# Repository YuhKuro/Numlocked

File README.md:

# Numlocked: Shift
 A 75% + 25% Keyboard with extras
 ## Features:
 - "standard" 75% ANSI US QWERTY Layout
 - Hot Swappable
 - Integrated Fingerprint Sensor
 - Leftside Numpad
 - Volume Knob, Dedicated Media Keys
 - Four extra keys above the keypad, nine extra F keys. 
 - Separate USB hub with two USB-A ports and one USB-C connection
 - 128x32 OLED
 
Front of Keyboard PCB:

Back of keyboard PCB:

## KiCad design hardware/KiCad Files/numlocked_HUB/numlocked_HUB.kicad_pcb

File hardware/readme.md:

# Hardware

## Table of Contents
- [Introduction](#introduction)
- [Keyboard Fundamentals](#keyboard-fundamentals)
- [HUB PCB](#hub-pcb)
- [Leftside PCB](#left-side-pcb)
- [Rightside PCB](#right-side-pcb)
- [Numpad PCB](numpad-pcb)

## Introduction
The keyboard consists of four PCBs: A USB-Hub and three PCBs for each part of the keyboard: Leftside, Rightside and Numpad.
Each component is connected via magnetic pogo pins to transmit Power, Ground, keyboard signals and LED signals.

## Keyboard Fundamentals
Although most keyboards use a matrix-and-diode system, this keyboard uses a Parallel-load Serial-Shift shift-register approach.

Think of it like a train with containers moving along a circular track. Each container represents a key position, and the train can either load or shift its contents.

When the train is in "Load" mode, each container is set based on whether its corresponding key is pressed. If a key is not pressed, the container remains full; if it's pressed, the container will empty its contents out. 

In "Shift" mode, the train moves each container along, allowing us to check them one by one and identify which keys are pressed by checking which containers are empty.

In this keyboard, all shift registers are pulled up to 3V3 through a 10k-ohm resistor, so each key naturally sits at a high (3.3V) state, much like a full train car. When a key is pressed, it ground that bit on the shift register, reading it as low. By shifting the bits in the register the exact number of keys and feeding the information into an array, we will have a snapshot of what keys are pressed in that cycle. 

Since the SN74HC165DR Shift Registers used in this keyboard allow clocking in the range of a few MHz, there is practically zero chance a key input is missed as the next "load" phase is a just a few microseconds away.

This system also allows for minimal debouncing, requires zero diodes, only requires three pins to read any number of keys and true n-key rollover.

### Why this method?
Using shift registers allows for overall less individual soldering, easier programming and most importantly, only requires three pins (SH/~LD, CLK and Serial-Out).
If we chain shift registers beginning with the removable parts, such as the numpad, and transmit the serial-out to the next removable part, such as the right side, and finally to the left-side, we can manage a system with only one MCU by using multiplexers to avoid unknown values. 

We can do this by using multiplexers, which are basically data switches, and schmitt triggers which help ensure a clear signal. By using the schmitt triggers, the multiplexers always have a clean input on which component is connected. 

The flow chart into the first shift register of the left side is the following:

The edge case of numpad connected, but no right side is handled in software.

## Hub PCB
The Hub PCB is centered around a one-to-four USB 2.0 Full Speed HUB. There is one upstream USB-C port which connects to the user's computer and three USB-A ports for other peripherals, as well as an FFC cable which connects it to the keyboard itself.

To minimize space used in the case, there is a notched hole on the PCB itself to allow the FFC Cable to connect between the Hub to the keyboard PCB even when the two PCBs may be flush.

## Left-Side PCB
The Left-Side PCB serves as the core of the keyboard’s functionality and is the only component capable of operating independently. This is due to the onboard RP2040 microcontroller, which manages all keyboard input processing. The Left-Side PCB features an FFC connector linking it to the USB Hub PCB, enabling seamless integration within the keyboard assembly.
The Left-Side PCB Features:
- FFC Connector to connect to the Hub
- RP2040 Microcontroller
	- 128 Mbit SPI Flash Memory
	- Crystal Oscillator
	- Header pins for Reset and USB Boot
- Five SN74HC165DR parallel-load serial-out shift registers to handle inputs
- Two four-pin magnetic pogo pins (2x4) to connect to the Numpad PCB.
- Three four-pin magnetic pogo pins (3x4) to connect to the Right-Side PCB
- Muxes and Debouncing Schmitt Triggers
- Real-time Clock (RTC) and CR1220 coin battery
### RP2040
The MCU for this keyboard is the RP2040, select for its cost, power efficiency and ease-of-programming, along with its plethora of GPIO pins and IO options. 

## Right-Side PCB
The Right-side PCB handles the right side of the keyboard's inputs and passes it the left-side of the keyboard.
Furthermore, the Right-Side PCB (if present) will also pass through the Numpad's data to the left side of the keyboard. This design was chosen to minimize the number of Magnetic Pogo Pin Connectors
## Numpad PCB
The Numpad PCB contains much of the same components as the Left-Side PCB.

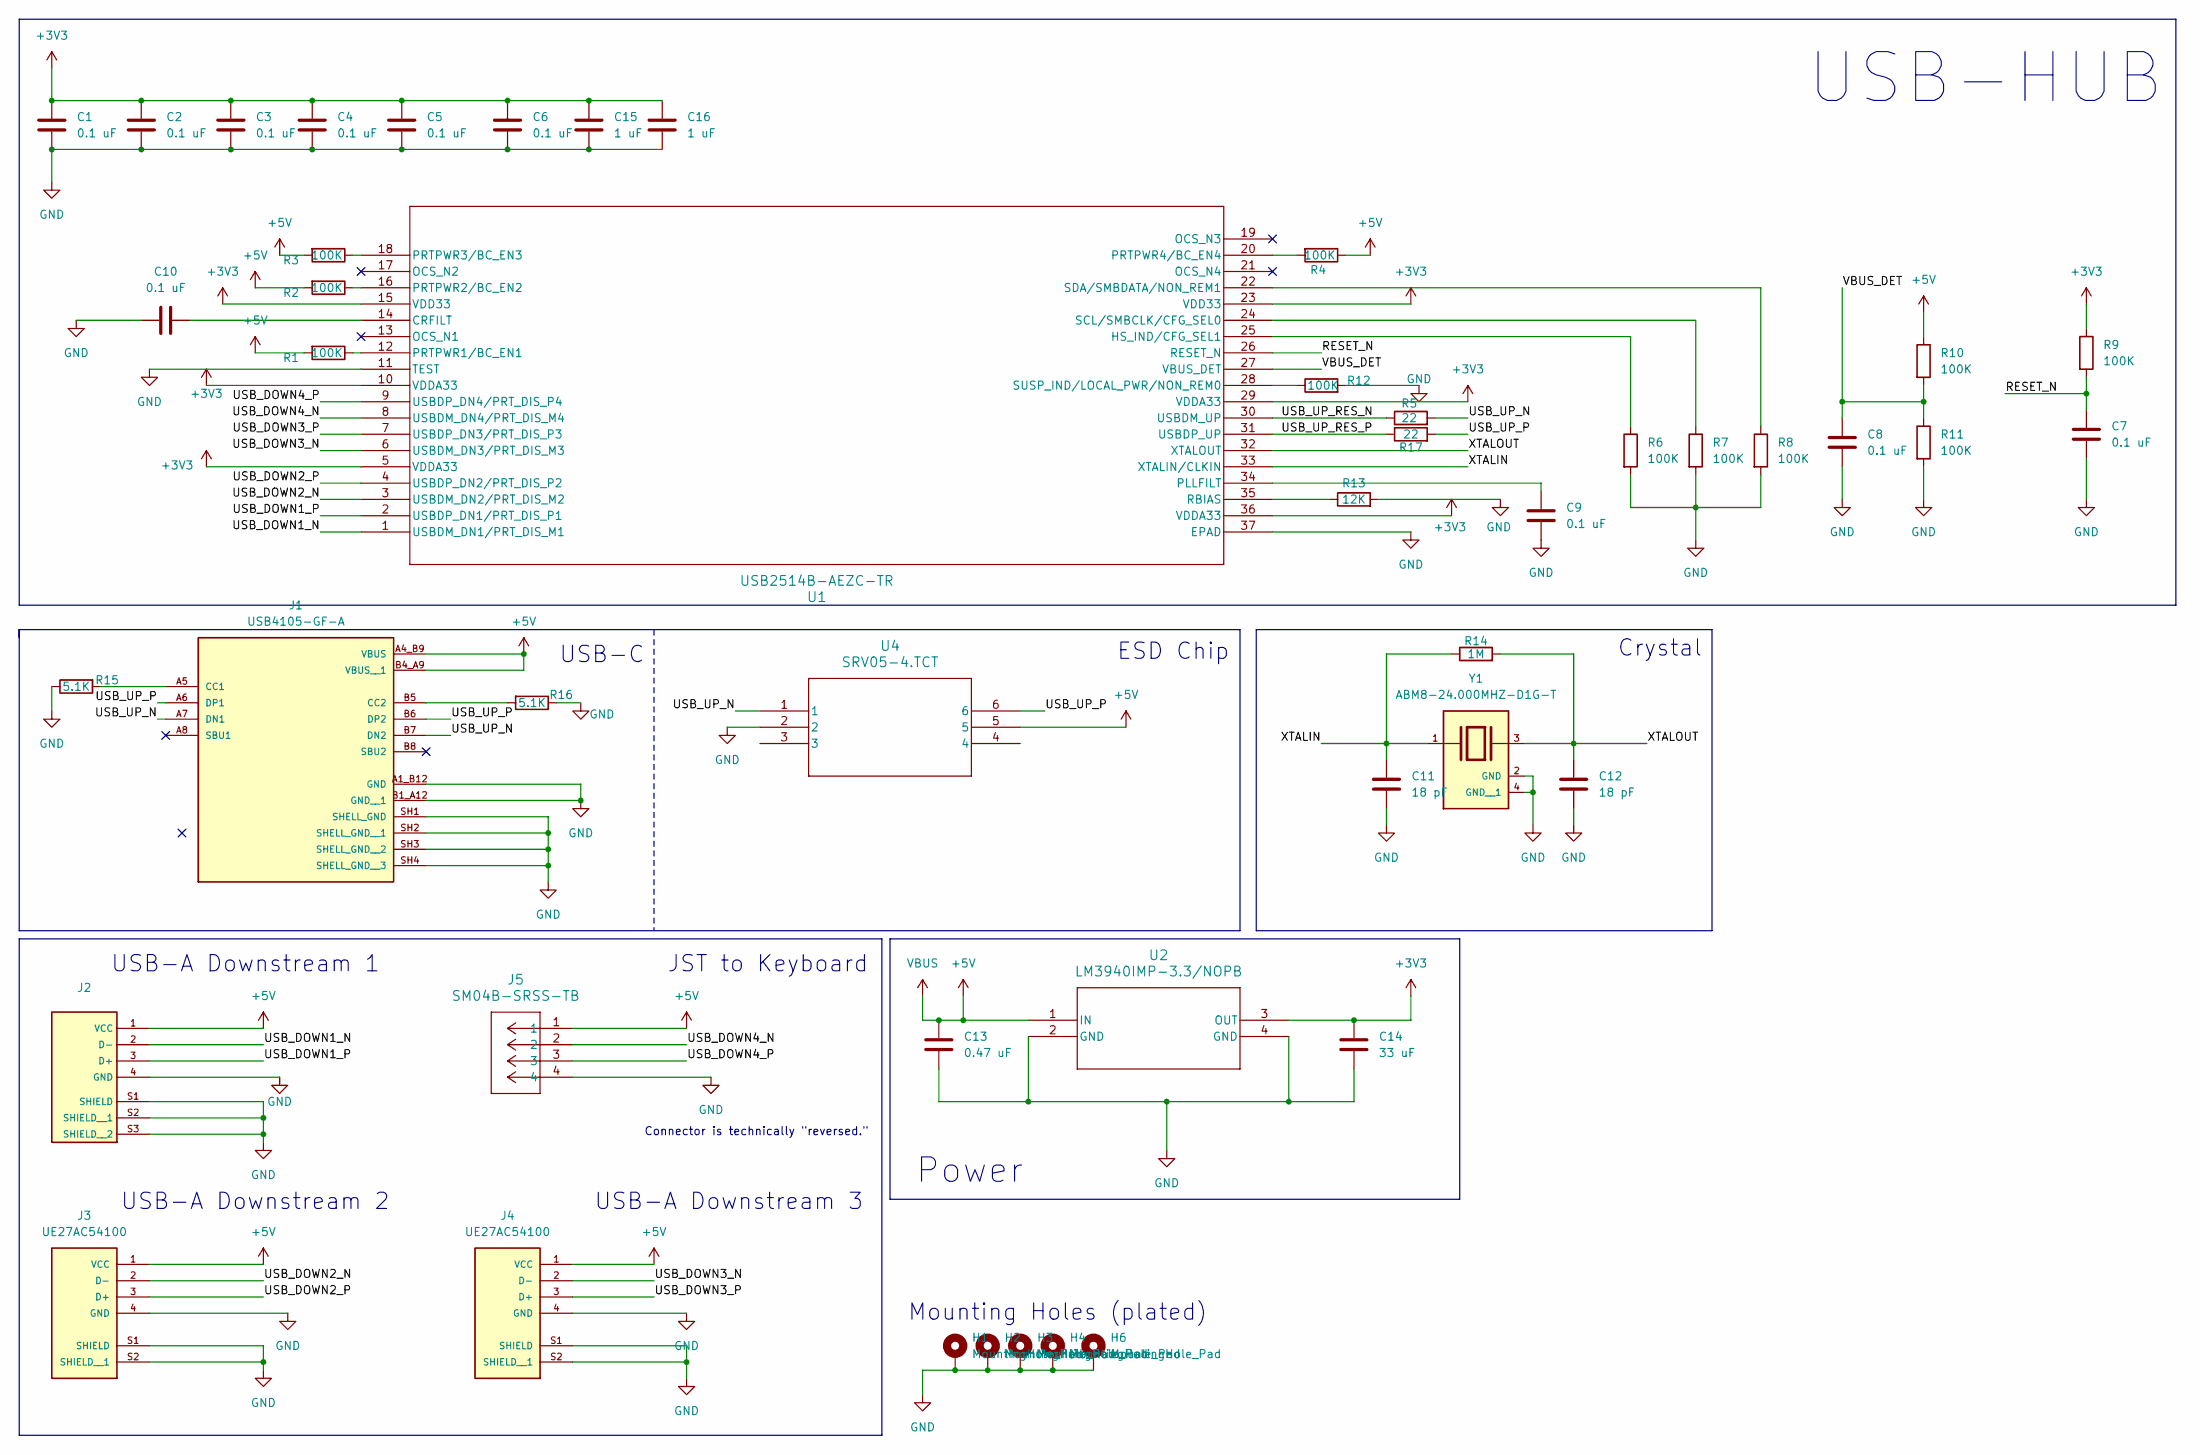
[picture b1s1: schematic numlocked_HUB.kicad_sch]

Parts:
C1, C2, C3, C4, C5, C6, C7, C8, C9, C10: 0.1 uF; C_0603_1608Metric
C11, C12: 18 pF; C_0603_1608Metric
C13: 0.47 uF; C_1206_3216Metric
C14: 33 uF; C_1206_3216Metric
C15, C16: 1 uF; C_0603_1608Metric
H1, H2, H3, H4, H6: MountingHole_Pad; MountingHole_2.2mm_M2_Pad
J1: USB4105-GF-A; GCT_USB4105-GF-A; PARTREV B4
J2: UBAS-4R-D14D-4D(LF)(SN)
J3, J4: UE27AC54100; AMPHENOL_UE27AC54100; PARTREV E
J5: SM04B-SRSS-TB; CONN_SM04B-SRSS-TB_JST
R1, R2, R3, R4, R6, R7, R8, R9, R10, R11, R12: 100K; R_0603_1608Metric
R5, R17: 22; R_0603_1608Metric
R13: 12K; R_0603_1608Metric
R14: 1M; R_0603_1608Metric
R15, R16: 5.1K; R_0603_1608Metric
U1: USB2514B-AEZC-TR; QFN36_6X6MC_MCH
U2: LM3940IMP-3.3/NOPB; SOT-223
U4: SRV05-4.TCT; SO6_SOT23-6L
Y1: ABM8-24.000MHZ-D1G-T; Crystal_SMD_Abracon_ABM8G-4Pin_3.2x2.5mm; PARTREV 44041

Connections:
+3V3: C1.1, C2.1, C3.1, C4.1, C5.1, C6.1, C14.1, C15.1, C16.1, R9.1, U1.5 (VDDA33), U1.10 (VDDA33), U1.15 (VDD33), U1.23 (VDD33), U1.29 (VDDA33), U1.36 (VDDA33), U2.3 (OUT)
+5V: C13.1, J1.A4_B9 (VBUS), J1.B4_A9 (VBUS__1), J2.1 (VCC), J3.1 (VCC), J4.1 (VCC), J5.1, R1.2, R2.2, R3.2, R4.1, R10.1, U2.1 (IN), U4.5
/RESET_N: C7.1, R9.2, U1.26 (RESET_N)
/USB_DOWN1_N: J2.2 (D-), U1.1 (USBDM_DN1/PRT_DIS_M1)
/USB_DOWN1_P: J2.3 (D+), U1.2 (USBDP_DN1/PRT_DIS_P1)
/USB_DOWN2_N: J3.2 (D-), U1.3 (USBDM_DN2/PRT_DIS_M2)
/USB_DOWN2_P: J3.3 (D+), U1.4 (USBDP_DN2/PRT_DIS_P2)
/USB_DOWN3_N: J4.2 (D-), U1.6 (USBDM_DN3/PRT_DIS_M3)
/USB_DOWN3_P: J4.3 (D+), U1.7 (USBDP_DN3/PRT_DIS_P3)
/USB_DOWN4_N: J5.2, U1.8 (USBDM_DN4/PRT_DIS_M4)
/USB_DOWN4_P: J5.3, U1.9 (USBDP_DN4/PRT_DIS_P4)
/USB_UP_N: J1.A7 (DN1), J1.B7 (DN2), R5.2, U4.1
/USB_UP_P: J1.A6 (DP1), J1.B6 (DP2), R17.2, U4.6
/USB_UP_RES_N: R5.1, U1.30 (USBDM_UP)
/USB_UP_RES_P: R17.1, U1.31 (USBDP_UP)
/VBUS_DET: C8.1, R10.2, R11.1, U1.27 (VBUS_DET)
/XTALIN: C11.1, R14.1, U1.33 (XTALIN/CLKIN), Y1.1
/XTALOUT: C12.1, R14.2, U1.32 (XTALOUT), Y1.3
GND: C1.2, C2.2, C3.2, C4.2, C5.2, C6.2, C7.2, C8.2, C9.2, C10.1, C11.2, C12.2, C13.2, C14.2, C15.2, C16.2, H1.1, H2.1, H3.1, H4.1, H6.1, J1.A1_B12 (GND), J1.B1_A12 (GND__1), J1.SH1 (SHELL_GND), J1.SH2 (SHELL_GND__1), J1.SH3 (SHELL_GND__2), J1.SH4 (SHELL_GND__3), J2.4 (GND), J2.S1 (SHIELD), J2.S2 (SHIELD__1), J2.S3 (SHIELD__2), J3.4 (GND), J3.S1 (SHIELD), J3.S2 (SHIELD__1), J4.4 (GND), J4.S1 (SHIELD), J4.S2 (SHIELD__1), J5.4, R6.2, R7.2, R8.2, R11.2, R12.2, R13.2, R15.1, R16.1, U1.11 (TEST), U1.37 (EPAD), U2.2 (GND), U2.4 (GND), U4.2, Y1.2 (GND), Y1.4 (GND__1); also elsewhere on the board
unnamed: J1.A5 (CC1), R15.2
unnamed: J1.B5 (CC2), R16.2
unnamed: C10.2, U1.14 (CRFILT)
unnamed: R6.1, U1.25 (HS_IND/CFG_SEL1)
unnamed: C9.1, U1.34 (PLLFILT)
unnamed: R1.1, U1.12 (PRTPWR1/BC_EN1)
unnamed: R2.1, U1.16 (PRTPWR2/BC_EN2)
unnamed: R3.1, U1.18 (PRTPWR3/BC_EN3)
unnamed: R4.2, U1.20 (PRTPWR4/BC_EN4)
unnamed: R13.1, U1.35 (RBIAS)
unnamed: R7.1, U1.24 (SCL/SMBCLK/CFG_SEL0)
unnamed: R8.1, U1.22 (SDA/SMBDATA/NON_REM1)
unnamed: R12.1, U1.28 (SUSP_IND/LOCAL_PWR/NON_REM0)

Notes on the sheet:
Crystal
USB-A Downstream 1
Power
USB-HUB
JST to Keyboard
USB-A Downstream 2
USB-A Downstream 3
Connector is technically "reversed."
ESD Chip
USB-C
Mounting Holes (plated)

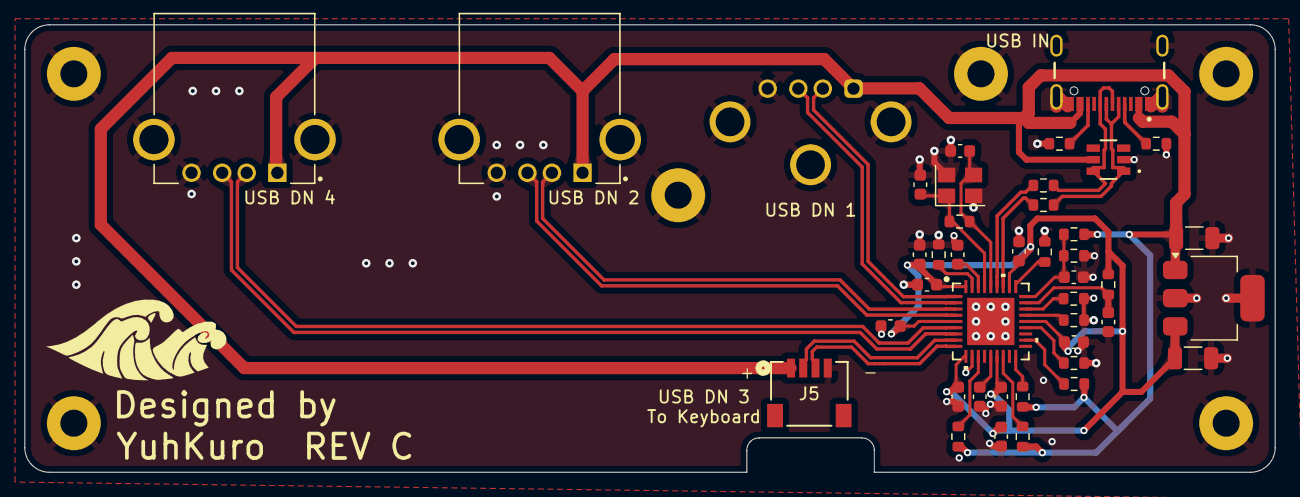
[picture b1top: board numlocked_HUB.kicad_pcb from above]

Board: 4 copper layers, 102.0 x 36.5 mm, 48 parts (1 on the bottom side), 32 nets.

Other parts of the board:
H2#2: MountingHole_Pad; MountingHole_2.2mm_M2_Pad

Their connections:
GND: H2#2.1; also elsewhere on the board

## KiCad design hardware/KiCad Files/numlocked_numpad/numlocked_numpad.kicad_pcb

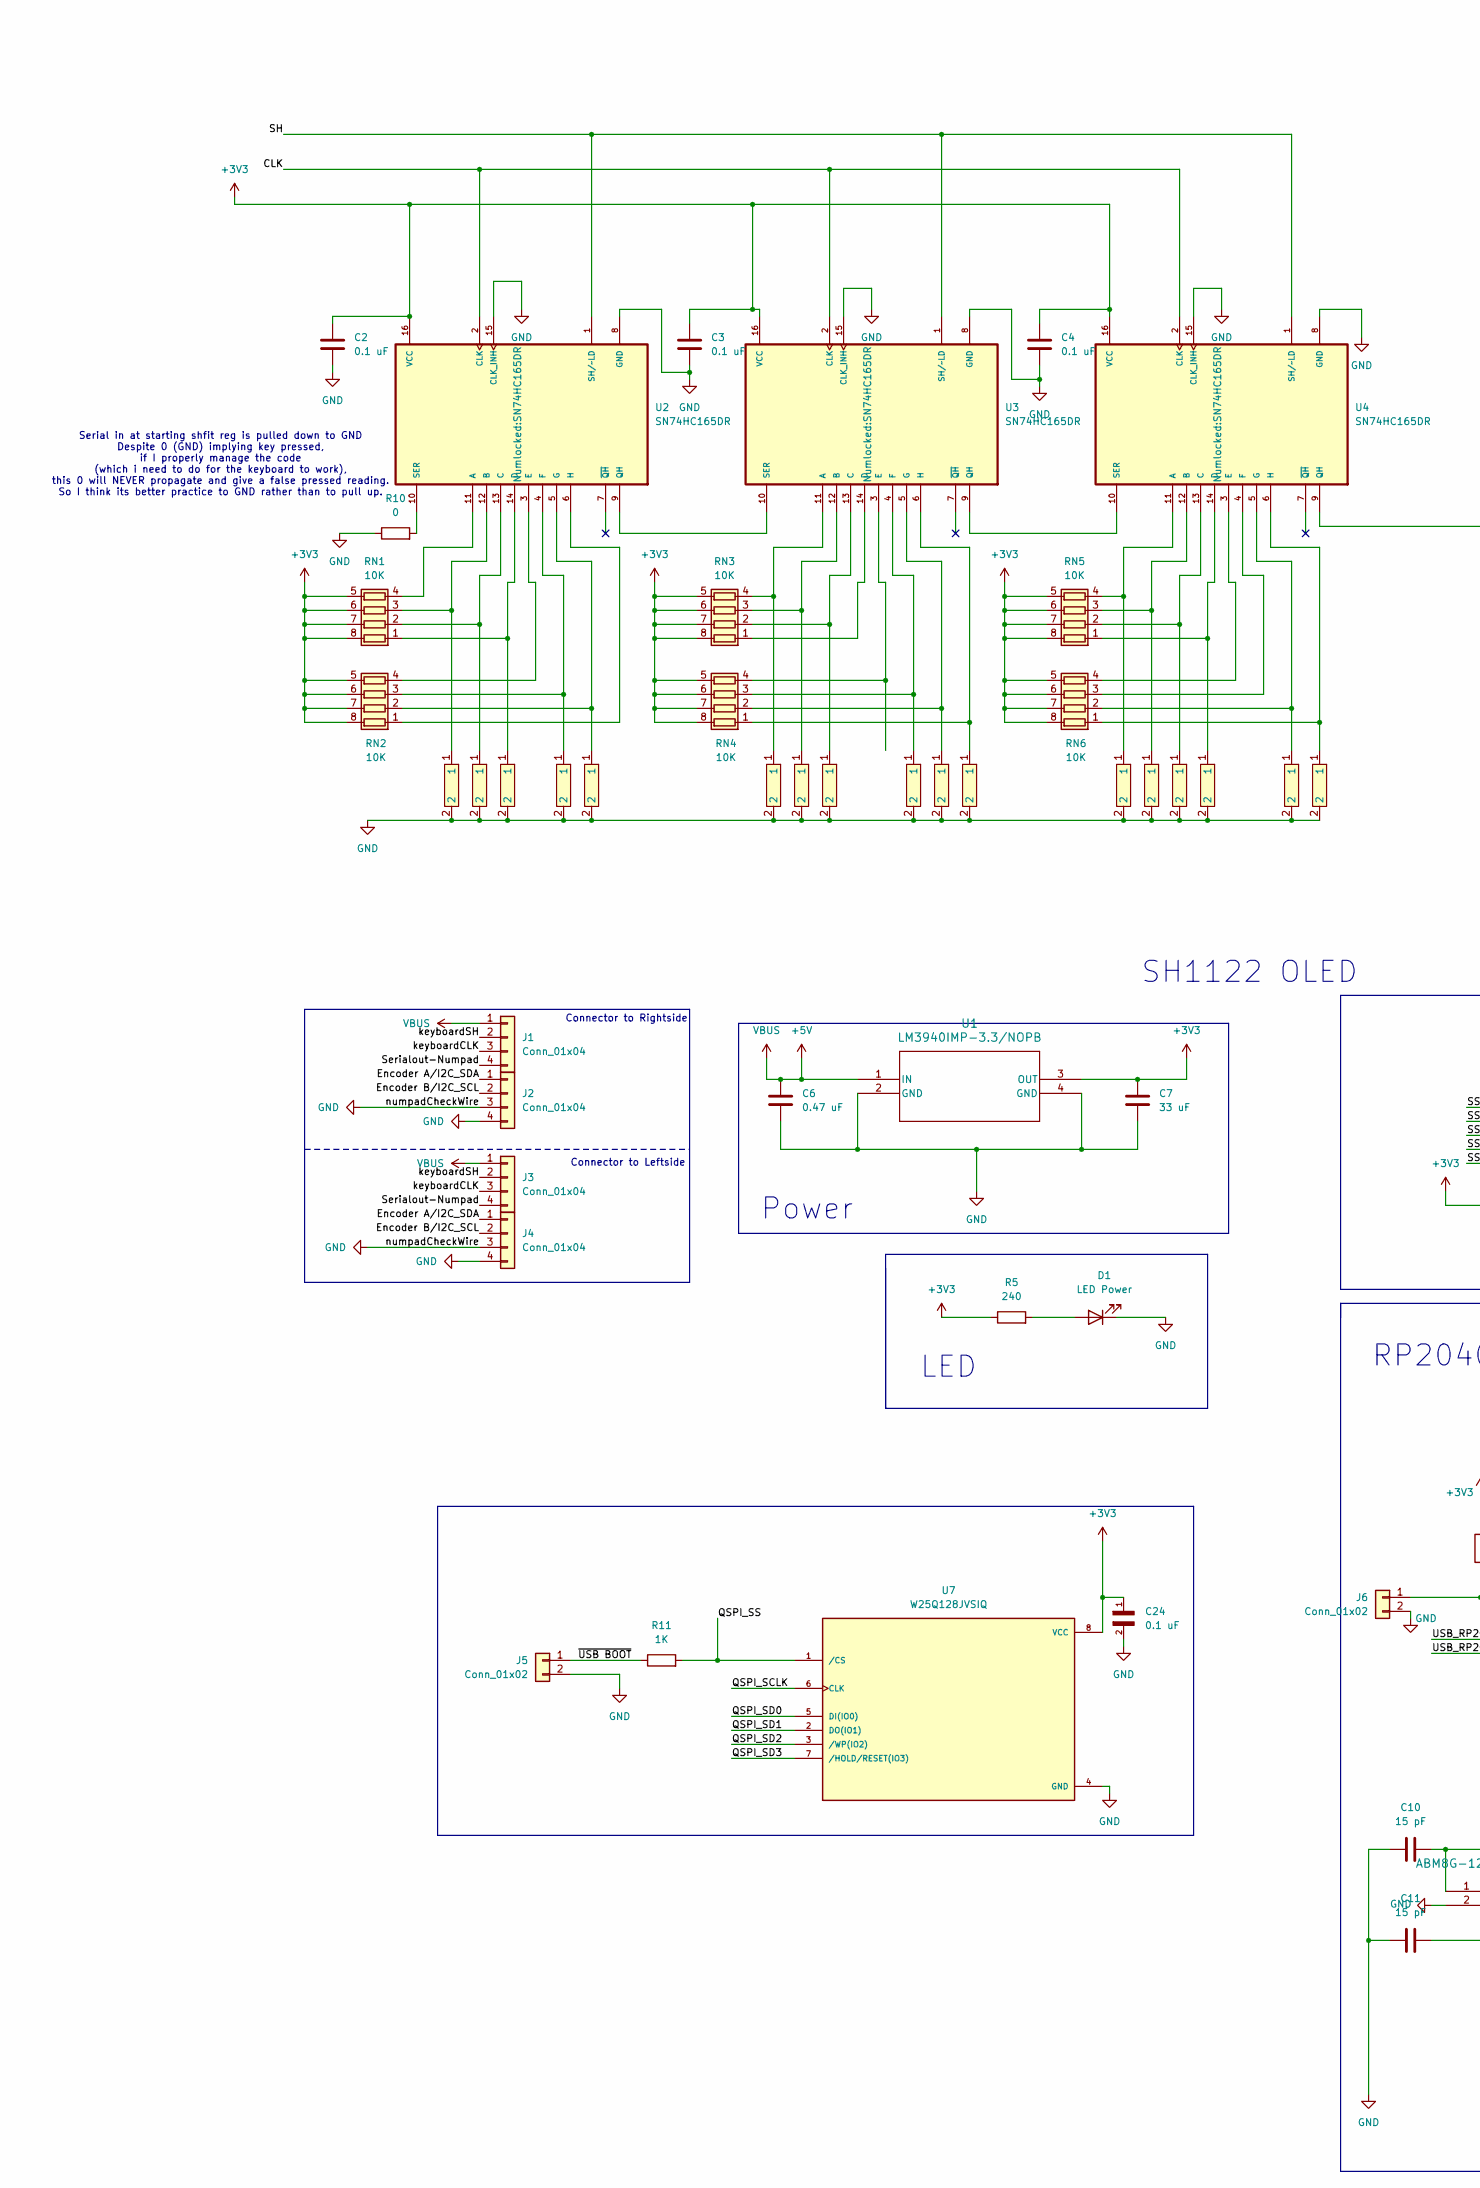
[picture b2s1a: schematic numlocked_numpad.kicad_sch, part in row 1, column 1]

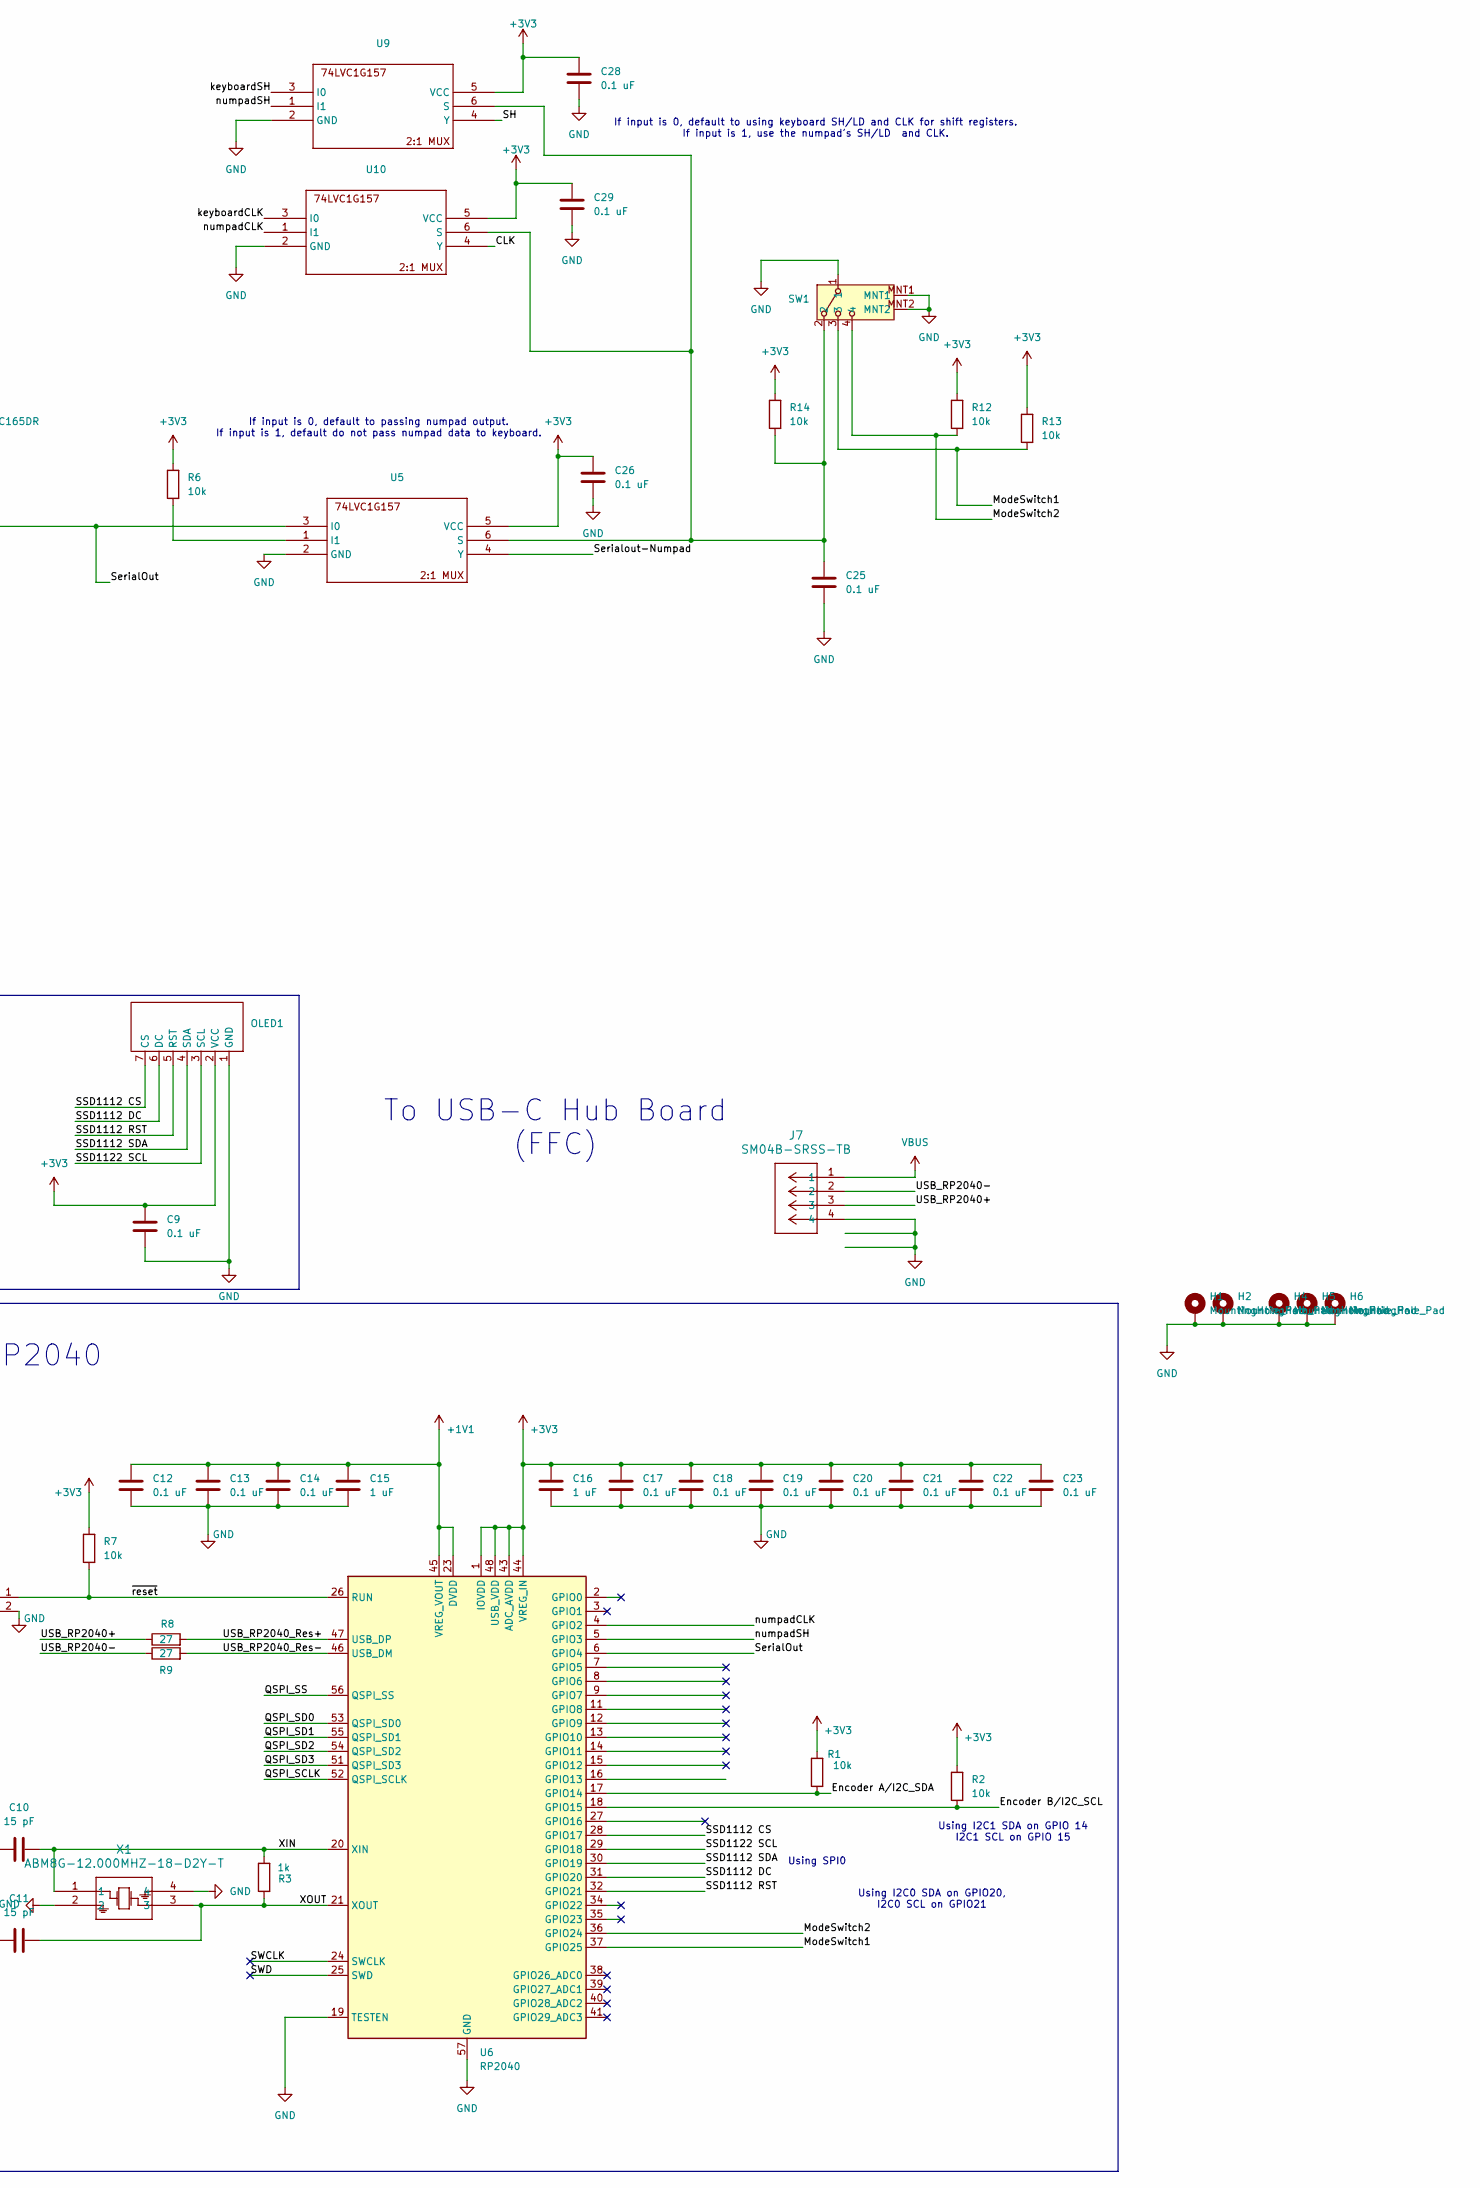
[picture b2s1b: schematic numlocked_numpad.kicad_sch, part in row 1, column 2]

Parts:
C2, C3, C4, C9, C12, C13, C14, C17, C18, C19, C20, C21, C22, C23, C25, C26, C28, C29: 0.1 uF; C_0603_1608Metric
C6: 0.47 uF; C_1206_3216Metric
C7: 33 uF; C_1206_3216Metric
C10, C11: 15 pF; C_0603_1608Metric
C15, C16: 1 uF; C_0603_1608Metric
C24: 0.1 uF; C_0603_1608Metric; PARTREV 8/11/2022
D1: LED Power; LED_0603_1608Metric
H1, H2, H4, H5, H6: MountingHole_Pad; MountingHole_2.2mm_M2_Pad
J1, J2, J3, J4: Conn_01x04; Magnetic_Pogo_Pin_4pos
J5, J6: Conn_01x02; PinSocket_1x02_P2.00mm_Vertical
J7: SM04B-SRSS-TB; CONN_SM04B-SRSS-TB_JST
OLED1: PinSocket_1x07_P2.54mm_Vertical
R1, R2, R6, R7, R12, R13, R14: 10k; R_0603_1608Metric
R3: 1k; R_0603_1608Metric
R5: 240; R_0603_1608Metric
R8, R9: 27; R_0603_1608Metric
R10: 0; R_0603_1608Metric
R11: 1K; R_0603_1608Metric
RN1, RN2, RN3, RN4, RN5, RN6: 10K; R_Array_Convex_4x1206
S1, S2, S3, S6, S8, S9, S10, S11, S12, S14, S16, S17, S18, S19: SW_Cherry_Kalih_1.00u
S7: SW_Cherry_Kalih_2.00u
S15, S20: SW_Cherry_Kalih_2.00u_vert
SW1: SK13D07VG4
U1: LM3940IMP-3.3/NOPB; SOT-223
U2, U3, U4: SN74HC165DR
U5, U9, U10: SC-74-6_1.55x2.9mm_P0.95mm
U6: RP2040; QFN-56-1EP_7x7mm_P0.4mm_EP3.2x3.2mm
U7: W25Q128JVSIQ; SOIC_128JVSIQ_WIN; PARTREV I
X1: ABM8G-12.000MHZ-18-D2Y-T; Crystal_SMD_Abracon_ABM8AIG-4Pin_3.2x2.5mm

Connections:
+1V1: C12.1, C13.1, C14.1, C15.1, U6.23 (DVDD), U6.45 (VREG_VOUT), U6.50 (DVDD)
+3V3: C2.1, C3.1, C4.1, C7.1, C9.1, C16.1, C17.1, C18.1, C19.1, C20.1, C21.1, C22.1, C23.1, C24.1, C26.1, C28.1, C29.1, OLED1.2 (VCC), R1.2, R2.2, R5.1, R6.2, R7.2, R12.2, R13.2, R14.2, RN1.5 (R4.2), RN1.6 (R3.2), RN1.7 (R2.2), RN1.8 (R1.2), RN2.5 (R4.2), RN2.6 (R3.2), RN2.7 (R2.2), RN2.8 (R1.2), RN3.5 (R4.2), RN3.6 (R3.2), RN3.7 (R2.2), RN3.8 (R1.2), RN4.5 (R4.2), RN4.6 (R3.2), RN4.7 (R2.2), RN4.8 (R1.2), RN5.5 (R4.2), RN5.6 (R3.2), RN5.7 (R2.2), RN5.8 (R1.2), RN6.5 (R4.2), RN6.6 (R3.2), RN6.7 (R2.2), RN6.8 (R1.2), U1.3 (OUT), U2.16 (VCC), U3.16 (VCC), U4.16 (VCC), U5.5 (VCC), U6.1 (IOVDD), U6.10 (IOVDD), U6.22 (IOVDD), U6.33 (IOVDD), U6.42 (IOVDD), U6.43 (ADC_AVDD), U6.44 (VREG_IN), U6.48 (USB_VDD), U6.49 (IOVDD), U7.8 (VCC), U9.5 (VCC), U10.5 (VCC); also elsewhere on the board
+5V: C6.1, J1.1, J3.1, J7.1, U1.1 (IN)
/CLK: U2.2 (CLK), U3.2 (CLK), U4.2 (CLK), U10.4 (Y)
/Encoder A/I2C_SDA: J2.1, J4.1, R1.1, U6.17 (GPIO14)
/Encoder B/I2C_SCL: J2.2, J4.2, R2.1, U6.18 (GPIO15)
/ModeSwitch1: R13.1, SW1.3, U6.37 (GPIO25)
/ModeSwitch2: R12.1, SW1.4, U6.36 (GPIO24)
/QSPI_SCLK: U6.52 (QSPI_SCLK), U7.6 (CLK)
/QSPI_SD0: U6.53 (QSPI_SD0), U7.5 (DI(IO0))
/QSPI_SD1: U6.55 (QSPI_SD1), U7.2 (DO(IO1))
/QSPI_SD2: U6.54 (QSPI_SD2), U7.3 (/WP(IO2))
/QSPI_SD3: U6.51 (QSPI_SD3), U7.7 (/HOLD/RESET(IO3))
/QSPI_SS: R11.2, U6.56 (QSPI_SS), U7.1 (/CS)
/SH: U2.1 (SH/~LD), U3.1 (SH/~LD), U4.1 (SH/~LD), U9.4 (Y)
/SSD1112 CS: OLED1.7 (CS), U6.28 (GPIO17)
/SSD1112 DC: OLED1.6 (DC), U6.31 (GPIO20)
/SSD1112 RST: OLED1.5 (RST), U6.32 (GPIO21)
/SSD1112 SDA: OLED1.4 (SDA), U6.30 (GPIO19)
/SSD1122 SCL: OLED1.3 (SCL), U6.29 (GPIO18)
/SWCLK: U6.24 (SWCLK)
/SWD: U6.25 (SWD)
/SerialOut: U4.9 (QH), U5.3 (I0), U6.6 (GPIO4)
/Serialout-Numpad: J1.4, J3.4, U5.4 (Y)
/USB_RP2040+: J7.3, R8.1
/USB_RP2040-: J7.2, R9.1
/USB_RP2040_Res+: R8.2, U6.47 (USB_DP)
/USB_RP2040_Res-: R9.2, U6.46 (USB_DM)
/keyboardCLK: J1.3, J3.3, U10.3 (I0)
/keyboardSH: J1.2, J3.2, U9.3 (I0)
/numpadCLK: U6.4 (GPIO2), U10.1 (I1)
/numpadSH: U6.5 (GPIO3), U9.1 (I1)
/~USB BOOT: J5.1, R11.1
/~reset: J6.1, R7.1, U6.26 (RUN)
GND: C2.2, C3.2, C4.2, C6.2, C7.2, C9.2, C10.1, C11.1, C12.2, C13.2, C14.2, C15.2, C16.2, C17.2, C18.2, C19.2, C20.2, C21.2, C22.2, C23.2, C24.2, C25.2, C26.2, C28.2, C29.2, D1.1 (K), H1.1, H2.1, H4.1, H5.1, H6.1, J2.3, J2.4, J4.3, J4.4, J5.2, J6.2, J7.4, OLED1.1 (GND), R10.1, S1.2, S2.2, S3.2, S6.2, S7.2, S8.2, S9.2, S10.2, S11.2, S12.2, S14.2, S15.2, S16.2, S17.2, S18.2, S19.2, S20.2, SW1.1, SW1.MNT1, SW1.MNT2, U1.2 (GND), U1.4 (GND), U2.8 (GND), U2.15 (CLK_INH), U3.8 (GND), U3.15 (CLK_INH), U4.8 (GND), U4.15 (CLK_INH), U5.2 (GND), U6.19 (TESTEN), U6.57 (GND), U7.4 (GND), U9.2 (GND), U10.2 (GND), X1.2, X1.4; also elsewhere on the board
unnamed: D1.2 (A), R5.2
unnamed: RN1.1 (R1.1), S1.1, U2.14 (D)
unnamed: RN1.2 (R2.1), S3.1, U2.13 (C)
unnamed: RN1.3 (R3.1), S2.1, U2.12 (B)
unnamed: RN1.4 (R4.1), U2.11 (A)
unnamed: RN2.1 (R1.1), U2.6 (H)
unnamed: RN2.2 (R2.1), S7.1, U2.5 (G)
unnamed: RN2.3 (R3.1), S6.1, U2.4 (F)
unnamed: RN2.4 (R4.1), U2.3 (E)
unnamed: RN3.1 (R1.1), U3.14 (D)
unnamed: RN3.2 (R2.1), S11.1, U3.13 (C)
unnamed: RN3.3 (R3.1), S10.1, U3.12 (B)
unnamed: RN3.4 (R4.1), S9.1, U3.11 (A)
unnamed: RN4.1 (R1.1), S8.1, U3.6 (H)
unnamed: RN4.2 (R2.1), S12.1, U3.5 (G)
unnamed: RN4.3 (R3.1), S14.1, U3.4 (F)
unnamed: RN4.4 (R4.1), U3.3 (E)
unnamed: RN5.1 (R1.1), S20.1, U4.14 (D)
unnamed: RN5.2 (R2.1), S19.1, U4.13 (C)
unnamed: RN5.3 (R3.1), S18.1, U4.12 (B)
unnamed: RN5.4 (R4.1), S17.1, U4.11 (A)
unnamed: RN6.1 (R1.1), S16.1, U4.6 (H)
unnamed: RN6.2 (R2.1), S15.1, U4.5 (G)
unnamed: RN6.3 (R3.1), U4.4 (F)
unnamed: RN6.4 (R4.1), U4.3 (E)
unnamed: U2.9 (QH), U3.10 (SER)
unnamed: R10.2, U2.10 (SER)
unnamed: U3.9 (QH), U4.10 (SER)
unnamed: R6.1, U5.1 (I1)
unnamed: C25.1, R14.1, SW1.2, U5.6 (S), U9.6 (S), U10.6 (S)

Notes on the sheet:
Power
Connector to Leftside
Serial in at starting shfit reg is pulled down to GND Despite 0 (GND) implying key pressed, if I properly manage the code (which i need to do for the keyboard to work), this 0 will NEVER propagate and give a false pressed reading. So I think its better practice to GND rather than to pull up.
SH1122 OLED
RP2040
If input is 0, default to using keyboard SH/LD and CLK for shift registers. If input is 1, use the numpad's SH/LD and CLK.
LED
Using SPI0
To USB-C Hub Board (FFC)
Using I2C0 SDA on GPIO20, I2C0 SCL on GPIO21
Using I2C1 SDA on GPIO 14 I2C1 SCL on GPIO 15
Connector to Rightside
If input is 0, default to passing numpad output. If input is 1, default do not pass numpad data to keyboard.

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
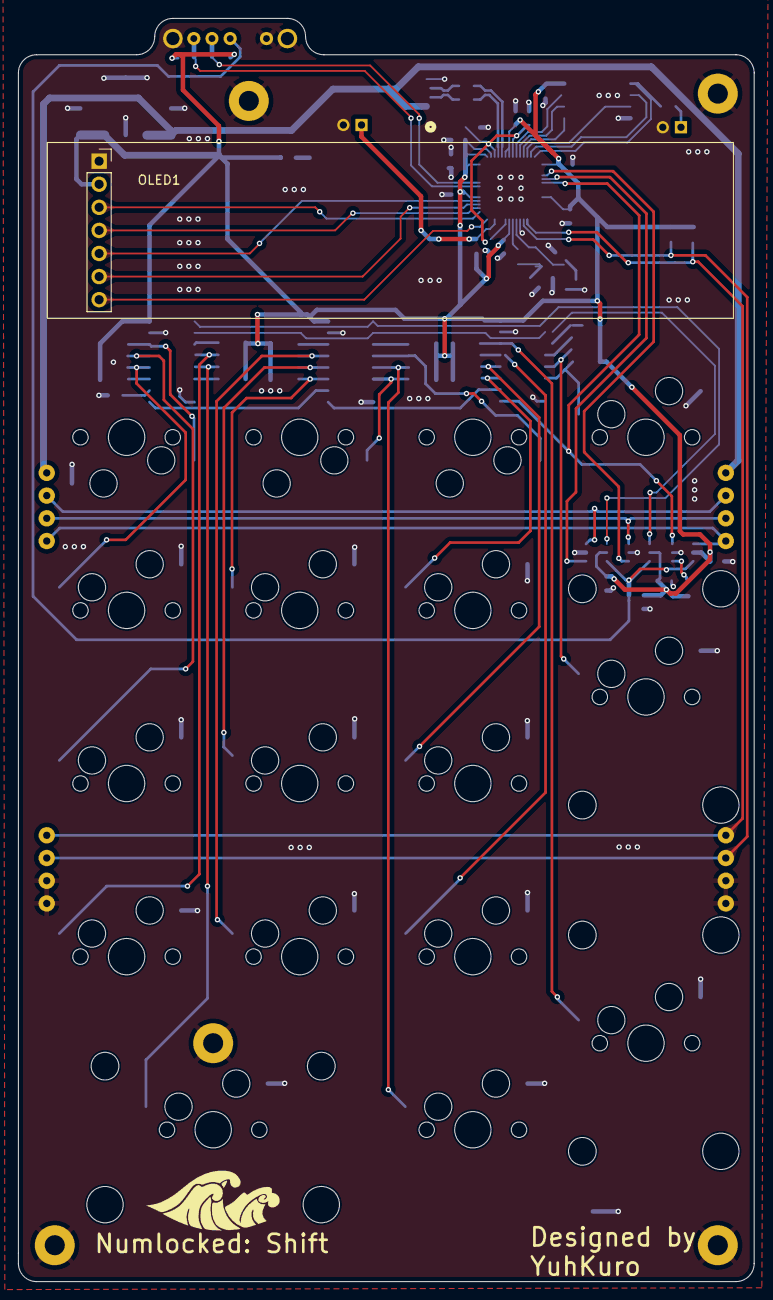
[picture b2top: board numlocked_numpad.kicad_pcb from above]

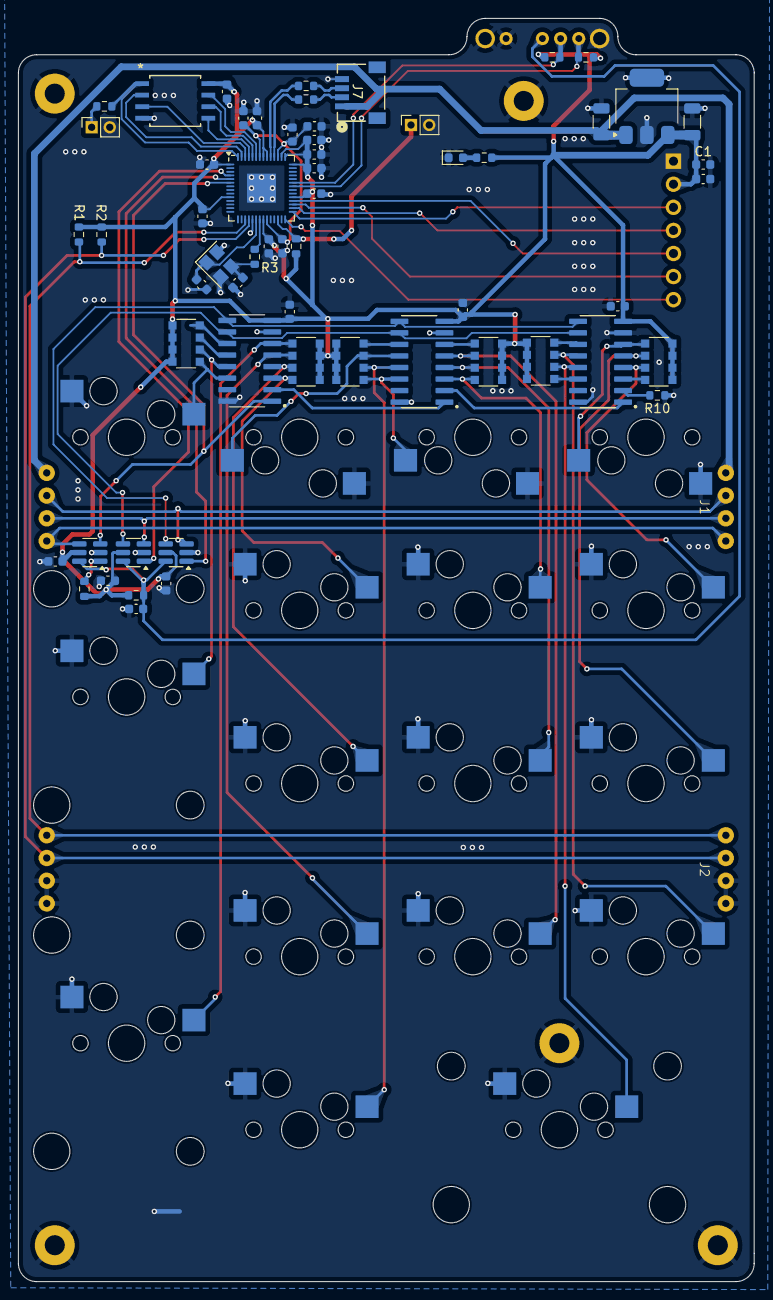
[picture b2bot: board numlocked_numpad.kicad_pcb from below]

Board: 4 copper layers, 81.0 x 139.0 mm, 87 parts (61 on the bottom side), 66 nets.

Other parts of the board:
C1: 10 uF; C_0603_1608Metric

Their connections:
+3V3: C1.1; also elsewhere on the board
GND: C1.2; also elsewhere on the board
